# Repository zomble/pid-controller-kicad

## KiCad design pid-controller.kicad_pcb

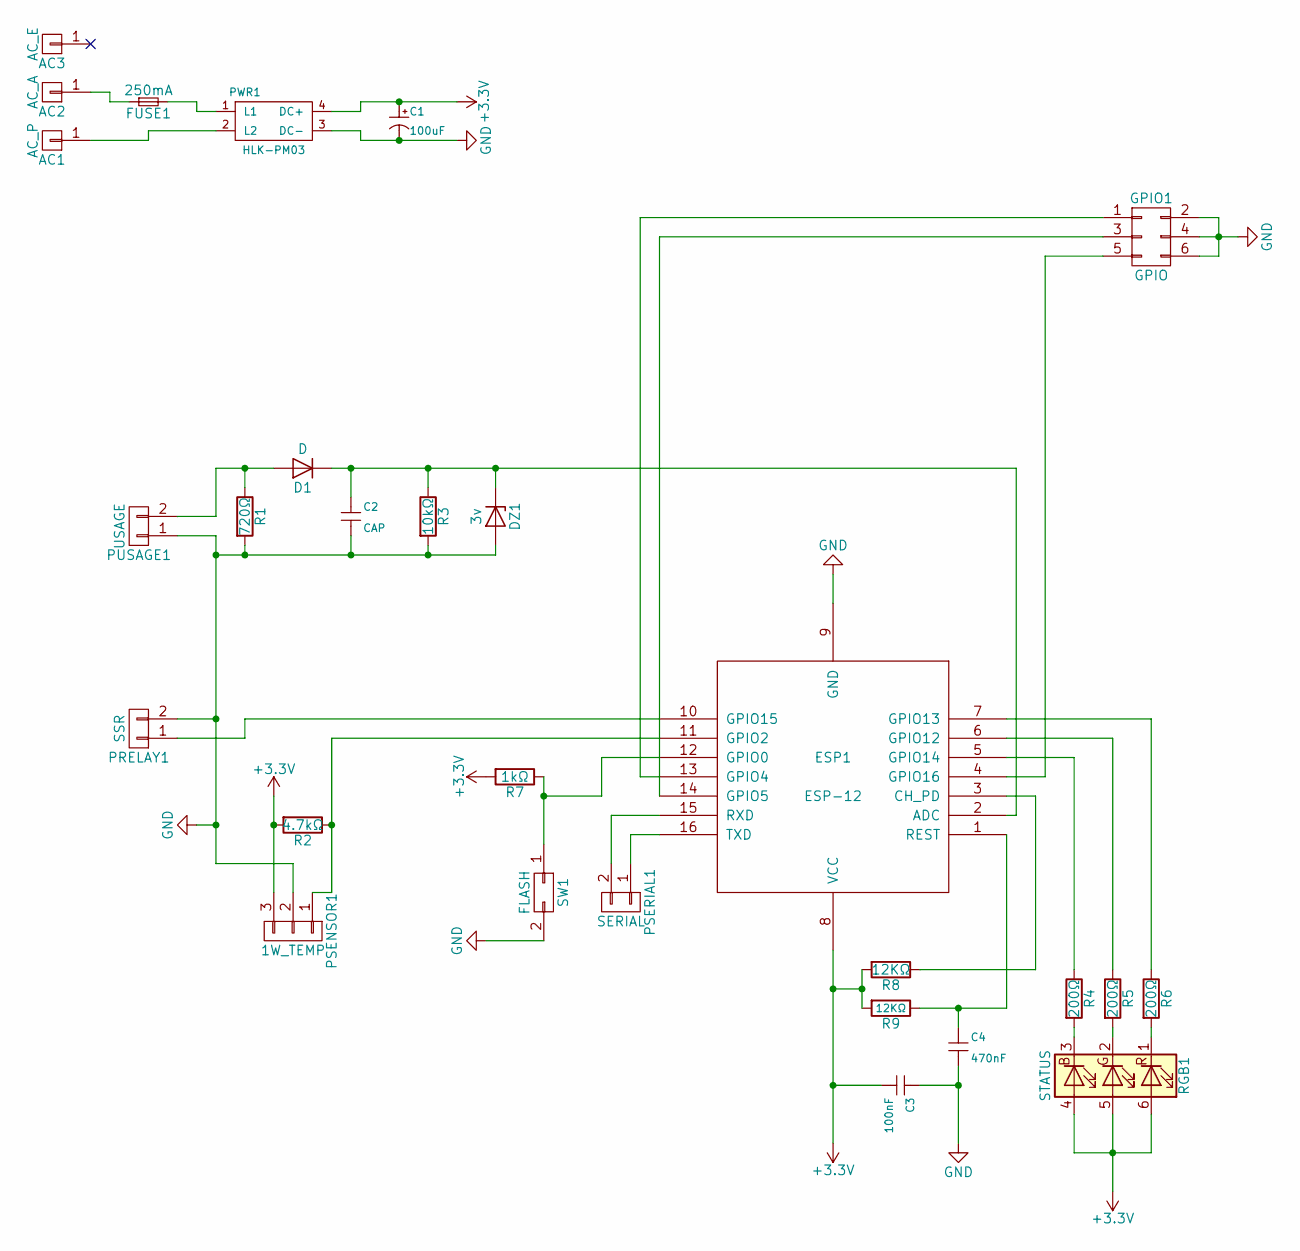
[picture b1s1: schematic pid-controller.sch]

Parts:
AC1: AC_P; Measurement_Point_Round-TH_Big
AC2: AC_A; Measurement_Point_Round-TH_Big
AC3: AC_E; Measurement_Point_Square-TH_Big
C1: 100uF; CP_Elec_8x10.5
C2: CAP; C_0805_HandSoldering
C3: 100nF; C_0805_HandSoldering
C4: 470nF; C_0805_HandSoldering
D1: D; D_SMB-SMC_Universal_Handsoldering
DZ1: 3v; D_SMB-SMC_Universal_Handsoldering
ESP1: ESP-12
FUSE1: 250mA; D_SMB-SMC_Universal_Handsoldering
GPIO1: GPIO; Pin_Header_Straight_2x03_Pitch2.54mm
PRELAY1: SSR; Pin_Header_Straight_1x02_Pitch2.54mm
PSENSOR1: 1W_TEMP; Pin_Header_Straight_1x03_Pitch2.54mm
PSERIAL1: SERIAL; Pin_Header_Straight_1x02_Pitch2.54mm
PUSAGE1: USAGE; Pin_Header_Straight_1x02_Pitch2.54mm
PWR1: HLK-PM03
R1: 720Ω; R_0805_HandSoldering
R2: 4.7kΩ; R_0805_HandSoldering
R3: 10kΩ; R_0805_HandSoldering
R4, R5, R6: 200Ω; R_0805_HandSoldering
R7: 1kΩ; R_0805_HandSoldering
R8, R9: 12KΩ; R_0805_HandSoldering
RGB1: STATUS; LED_WS2812-PLCC6
SW1: FLASH; Pin_Header_Straight_1x02_Pitch2.54mm

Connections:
+3V3: C1.1, C3.2, ESP1.8 (VCC), PSENSOR1.3, PWR1.4 (DC+), R2.2, R7.2, R8.2, R9.2, RGB1.4 (BA), RGB1.5 (GA), RGB1.6 (RA)
GND: C1.2, C2.2, C3.1, C4.2, DZ1.2 (A), ESP1.9 (GND), GPIO1.2, GPIO1.4, GPIO1.6, PRELAY1.2, PSENSOR1.2, PUSAGE1.1, PWR1.3 (DC-), R1.2, R3.2, SW1.2
unnamed: AC1.1, PWR1.2 (L2)
unnamed: AC2.1, FUSE1.1
unnamed: C2.1, D1.1 (K), DZ1.1 (K), ESP1.2 (ADC), R3.1
unnamed: C4.1, ESP1.1 (REST), R9.1
unnamed: D1.2 (A), PUSAGE1.2, R1.1
unnamed: ESP1.3 (CH_PD), R8.1
unnamed: ESP1.4 (GPIO16), GPIO1.5
unnamed: ESP1.5 (GPIO14), R4.1
unnamed: ESP1.6 (GPIO12), R5.1
unnamed: ESP1.7 (GPIO13), R6.1
unnamed: ESP1.10 (GPIO15), PRELAY1.1
unnamed: ESP1.11 (GPIO2), PSENSOR1.1, R2.1
unnamed: ESP1.12 (GPIO0), R7.1, SW1.1
unnamed: ESP1.13 (GPIO4), GPIO1.1
unnamed: ESP1.14 (GPIO5), GPIO1.3
unnamed: ESP1.15 (RXD), PSERIAL1.2
unnamed: ESP1.16 (TXD), PSERIAL1.1
unnamed: FUSE1.2, PWR1.1 (L1)
unnamed: R4.2, RGB1.3 (BK)
unnamed: R5.2, RGB1.2 (GK)
unnamed: R6.2, RGB1.1 (RK)

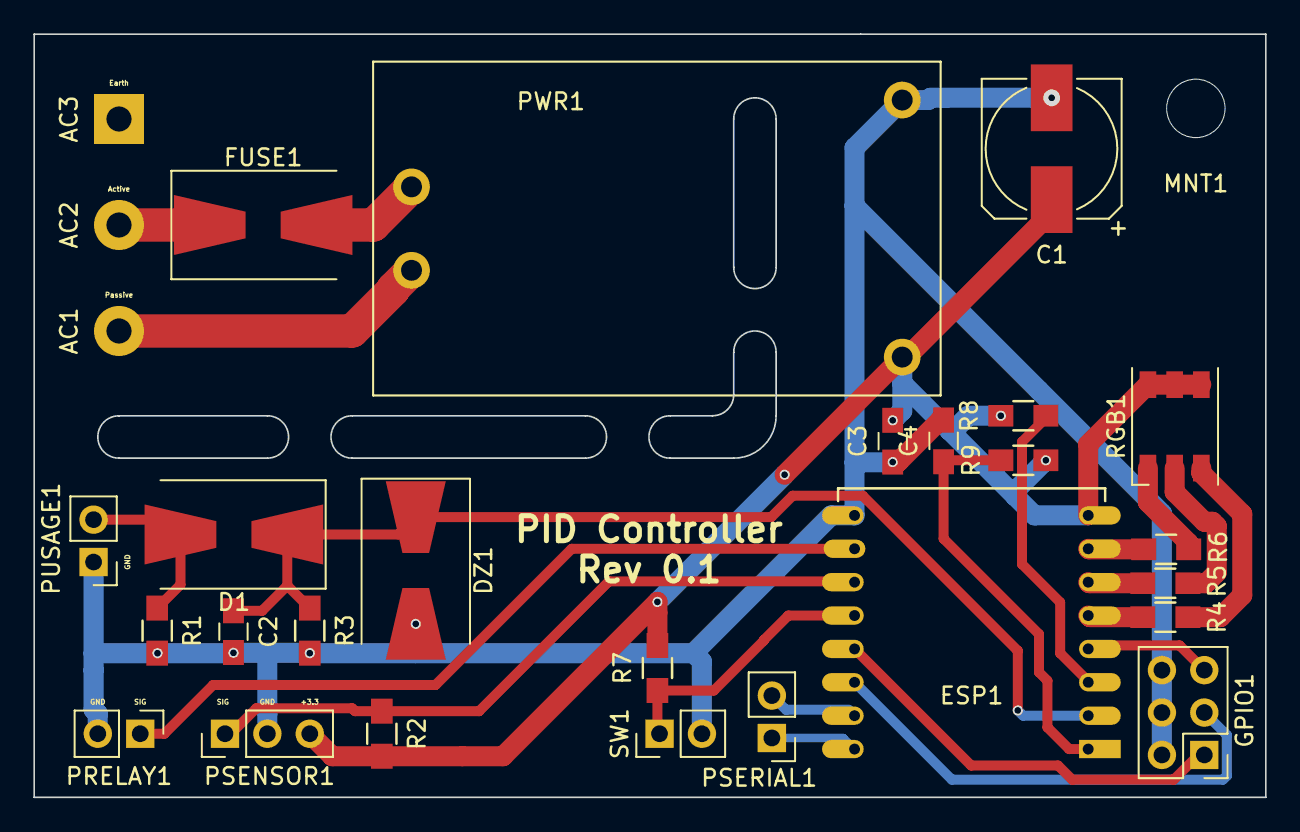
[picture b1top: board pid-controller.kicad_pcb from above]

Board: 2 copper layers, 73.8 x 45.7 mm, 29 parts (0 on the bottom side), 23 nets.

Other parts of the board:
MNT1: MountingHole_3.5mm

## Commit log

2017-03-17 revision 0.1
